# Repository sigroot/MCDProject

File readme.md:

This project is to design a MC68K based microcomputer on a single board.

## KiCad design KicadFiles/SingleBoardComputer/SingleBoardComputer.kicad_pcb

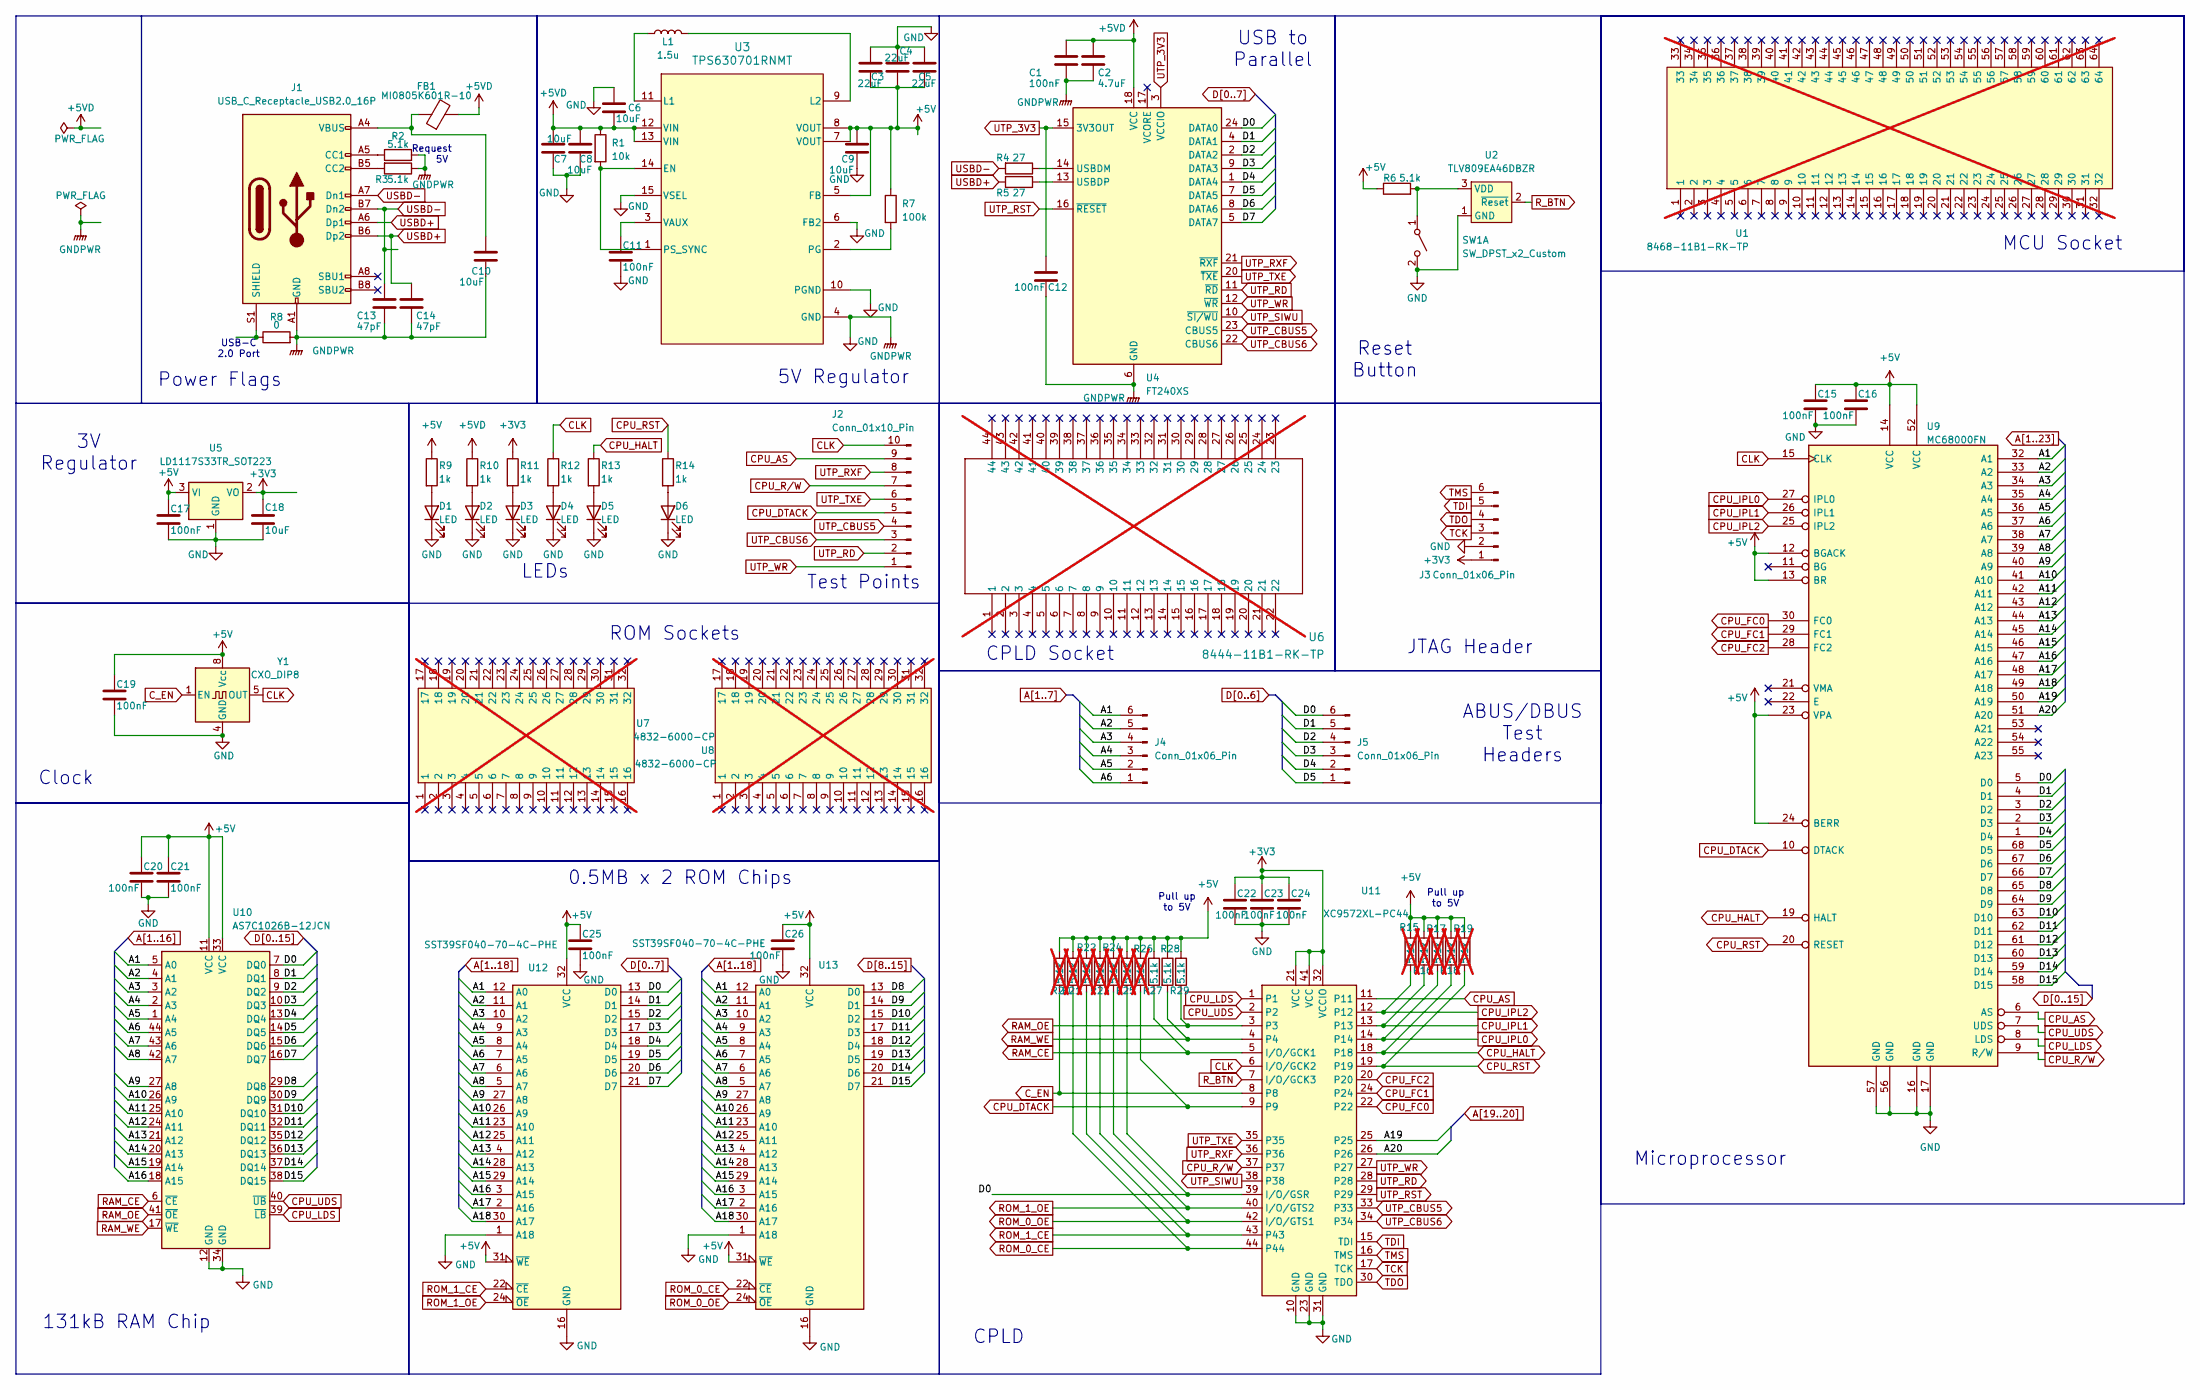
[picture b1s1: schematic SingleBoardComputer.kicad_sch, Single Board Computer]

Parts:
C1, C12, C15, C16, C17, C19, C20, C21, C22, C23, C24, C25, C26: 100nF; C_0603_1608Metric_Pad1.08x0.95mm_HandSolder
C2: 4.7uF; C_0603_1608Metric_Pad1.08x0.95mm_HandSolder
C3, C4, C5: 22uF; C_0805_2012Metric_Pad1.18x1.45mm_HandSolder
C6, C9: 10uF; C_0603_1608Metric_Pad1.08x0.95mm_HandSolder
C7, C8, C10, C18: 10uF; C_0805_2012Metric_Pad1.18x1.45mm_HandSolder
C11: 100nF; C_0402_1005Metric_Pad0.74x0.62mm_HandSolder; LCSC PN C155422
C13, C14: 47pF; C_0805_2012Metric_Pad1.18x1.45mm_HandSolder
D1, D2, D3, D4, D5, D6: LED; LED_0805_2012Metric_Pad1.15x1.40mm_HandSolder
FB1: MI0805K601R-10; L_0805_2012Metric_Pad1.15x1.40mm_HandSolder
J1: USB_C_Receptacle_USB2.0_16P; CUI_UJ20-C-V-C-3-SMT-TR
J2: Conn_01x10_Pin; PinHeader_1x10_P2.54mm_Vertical
J3, J4, J5: Conn_01x06_Pin; PinHeader_1x06_P2.54mm_Vertical
L1: 1.5u; L_Coilcraft_XxL4020; LCSC PN C3033018
R1: 10k; R_0805_2012Metric_Pad1.20x1.40mm_HandSolder
R2, R3, R6, R27, R28, R29: 5.1k; R_0805_2012Metric_Pad1.20x1.40mm_HandSolder
R4, R5: 27; R_0805_2012Metric_Pad1.20x1.40mm_HandSolder
R7: 100k; R_0805_2012Metric_Pad1.20x1.40mm_HandSolder
R8: 0; R_0805_2012Metric_Pad1.20x1.40mm_HandSolder
R9, R10, R11, R12, R13, R14: 1k; R_0805_2012Metric_Pad1.20x1.40mm_HandSolder
R15, R16, R17, R18, R19, R20, R21, R22, R23, R24, R25, R26: 5.1k; R_0805_2012Metric_Pad1.20x1.40mm_HandSolder; not fitted
SW1: SW_DPST_x2_Custom; SW_SPST_PTS647_Sx38
U1: 8468-11B1-RK-TP; PLCC-68_THT-Socket; not fitted
U2: TLV809EA46DBZR; SOT-23
U3: TPS630701RNMT; RNM0015A; LCSC PN C181473
U4: FT240XS; SSOP-24_3.9x8.7mm_P0.635mm; LCSC PN C69082
U5: LD1117S33TR_SOT223; SOT-223-3_TabPin2; LCSC PN LD1117S33TR
U6: 8444-11B1-RK-TP; TO_11B1-RK-TP_3MM; not fitted
U7, U8: 4832-6000-CP; DIP-32_W15.24mm_Socket; not fitted
U9: MC68000FN; PLCC-68_THT-Socket
U10: AS7C1026B-12JCN; SOJ-44_10.16x28.575mm_P1.27mm
U11: XC9572XL-PC44; PLCC-44_THT-Socket
U12, U13: SST39SF040-70-4C-PHE; DIP-32_W15.24mm_Socket_LongPads
Y1: CXO_DIP8; Oscillator_DIP-8

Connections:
+3V3: C18.1, C22.1, C23.1, C24.1, J3.1, R11.1, U5.2 (VO), U11.21 (VCC), U11.32 (VCCIO), U11.41 (VCC)
+5V: C3.2, C4.2, C5.2, C9.1, C15.1, C16.1, C17.1, C19.1, C20.1, C21.1, C25.1, C26.1, R6.1, R7.1, R9.1, R15.1, R16.1, R17.1, R18.1, R19.1, R20.1, R21.1, R22.1, R23.1, R24.1, R25.1, R26.1, R27.1, R28.1, R29.1, U3.5 (FB), U3.7 (VOUT), U3.8 (VOUT), U5.3 (VI), U9.12 (BGACK), U9.13 (BR), U9.14 (VCC), U9.23 (VPA), U9.24 (BERR), U9.52 (VCC), U10.11 (VCC), U10.33 (VCC), U12.31 (~WE), U12.32 (VCC), U13.31 (~WE), U13.32 (VCC), Y1.8 (Vcc)
+5VD: C1.1, C2.1, C6.2, C7.1, C8.1, FB1.2, R1.1, R10.1, U3.12 (VIN), U3.13 (VIN), U4.18 (VCC)
A1: J4.6, U9.32 (A1), U10.5 (A0), U12.12 (A0), U13.12 (A0)
A2: J4.5, U9.33 (A2), U10.4 (A1), U12.11 (A1), U13.11 (A1)
A3: J4.4, U9.34 (A3), U10.3 (A2), U12.10 (A2), U13.10 (A2)
A4: J4.3, U9.35 (A4), U10.2 (A3), U12.9 (A3), U13.9 (A3)
A5: J4.2, U9.36 (A5), U10.1 (A4), U12.8 (A4), U13.8 (A4)
A6: J4.1, U9.37 (A6), U10.44 (A5), U12.7 (A5), U13.7 (A5)
A7: U9.38 (A7), U10.43 (A6), U12.6 (A6), U13.6 (A6)
A8: U9.39 (A8), U10.42 (A7), U12.5 (A7), U13.5 (A7)
A9: U9.40 (A9), U10.27 (A8), U12.27 (A8), U13.27 (A8)
A10: U9.41 (A10), U10.26 (A9), U12.26 (A9), U13.26 (A9)
A11: U9.42 (A11), U10.25 (A10), U12.23 (A10), U13.23 (A10)
A12: U9.43 (A12), U10.24 (A11), U12.25 (A11), U13.25 (A11)
A13: U9.44 (A13), U10.21 (A12), U12.4 (A12), U13.4 (A12)
A14: U9.45 (A14), U10.20 (A13), U12.28 (A13), U13.28 (A13)
A15: U9.46 (A15), U10.19 (A14), U12.29 (A14), U13.29 (A14)
A16: U9.47 (A16), U10.18 (A15), U12.3 (A15), U13.3 (A15)
A17: U9.48 (A17), U12.2 (A16), U13.2 (A16)
A18: U9.49 (A18), U12.30 (A17), U13.30 (A17)
A19: U9.50 (A19), U11.25
A20: U9.51 (A20), U11.26
CLK: J2.10, R12.1, U9.15 (CLK), U11.6 (I/O/GCK2), Y1.5 (OUT)
CPU_AS: J2.9, U9.6 (AS), U11.11
CPU_DTACK: J2.5, R26.2, U9.10 (DTACK), U11.9
CPU_FC0: U9.30 (FC0), U11.22
CPU_FC1: U9.29 (FC1), U11.24
CPU_FC2: U9.28 (FC2), U11.20
CPU_HALT: R13.1, R18.2, U9.19 (HALT), U11.18
CPU_IPL0: R17.2, U9.27 (IPL0), U11.14
CPU_IPL1: R16.2, U9.26 (IPL1), U11.13
CPU_IPL2: R15.2, U9.25 (IPL2), U11.12
CPU_LDS: U9.8 (LDS), U10.39 (~LB), U11.1
CPU_RST: R14.1, R19.2, U9.20 (RESET), U11.19
CPU_R/W: J2.7, U9.9 (R/W), U11.37
CPU_UDS: U9.7 (UDS), U10.40 (~UB), U11.2
C_EN: R20.2, U11.8, Y1.1 (EN)
D0: J5.6, R25.2, U4.24 (DATA0), U9.5 (D0), U10.7 (DQ0), U11.39 (I/O/GSR), U12.13 (D0)
D1: J5.5, U4.4 (DATA1), U9.4 (D1), U10.8 (DQ1), U12.14 (D1)
D2: J5.4, U4.2 (DATA2), U9.3 (D2), U10.9 (DQ2), U12.15 (D2)
D3: J5.3, U4.9 (DATA3), U9.2 (D3), U10.10 (DQ3), U12.17 (D3)
D4: J5.2, U4.1 (DATA4), U9.1 (D4), U10.13 (DQ4), U12.18 (D4)
D5: J5.1, U4.7 (DATA5), U9.68 (D5), U10.14 (DQ5), U12.19 (D5)
D6: U4.8 (DATA6), U9.67 (D6), U10.15 (DQ6), U12.20 (D6)
D7: U4.5 (DATA7), U9.66 (D7), U10.16 (DQ7), U12.21 (D7)
D8: U9.65 (D8), U10.29 (DQ8), U13.13 (D0)
D9: U9.64 (D9), U10.30 (DQ9), U13.14 (D1)
D10: U9.63 (D10), U10.31 (DQ10), U13.15 (D2)
D11: U9.62 (D11), U10.32 (DQ11), U13.17 (D3)
D12: U9.61 (D12), U10.35 (DQ12), U13.18 (D4)
D13: U9.60 (D13), U10.36 (DQ13), U13.19 (D5)
D14: U9.59 (D14), U10.37 (DQ14), U13.20 (D6)
D15: U9.58 (D15), U10.38 (DQ15), U13.21 (D7)
GND: C1.2, C2.2, C3.1, C4.1, C5.1, C6.1, C7.2, C8.2, C9.2, C10.2, C11.2, C12.2, C13.2, C14.2, C15.2, C16.2, C17.2, C18.2, C19.2, C20.2, C21.2, C22.2, C23.2, C24.2, C25.2, C26.2, D1.1 (K), D2.1 (K), D3.1 (K), D4.1 (K), D5.1 (K), D6.1 (K), J1.A1 (GND), J1.A12 (GND), J1.B1 (GND), J1.B12 (GND), J3.2, R2.2, R3.1, R8.2, SW1.2 (B), U2.1 (GND), U3.4 (GND), U3.6 (FB2), U3.10 (PGND), U3.15 (VSEL), U4.6 (GND), U4.19 (GND), U5.1 (GND), U9.16 (GND), U9.17 (GND), U9.56 (GND), U9.57 (GND), U10.12 (GND), U10.34 (GND), U11.10 (GND), U11.23 (GND), U11.31 (GND), U12.1 (A18), U12.16 (GND), U13.1 (A18), U13.16 (GND), Y1.4 (GND)
unnamed: C10.1, FB1.1, J1.A4 (VBUS), J1.A9 (VBUS), J1.B4 (VBUS), J1.B9 (VBUS)
unnamed: D1.2 (A), R9.2
unnamed: D2.2 (A), R10.2
unnamed: D3.2 (A), R11.2
unnamed: D4.2 (A), R12.2
unnamed: D5.2 (A), R13.2
unnamed: D6.2 (A), R14.2
unnamed: J1.A5 (CC1), R2.1
unnamed: J1.B5 (CC2), R3.2
unnamed: J1.S1 (SHIELD), R8.1
unnamed: R6.2, SW1.1 (A), U2.3 (VDD)
unnamed: R1.2, U3.1 (PS_SYNC), U3.14 (EN)
unnamed: L1.1, U3.11 (L1)
unnamed: L1.2, U3.9 (L2)
unnamed: R7.2, U3.2 (PG)
unnamed: C11.1, U3.3 (VAUX)
unnamed: R4.1, U4.14 (USBDM)
unnamed: R5.1, U4.13 (USBDP)
RAM_CE: R27.2, U10.6 (~CE), U11.5 (I/O/GCK1)
RAM_OE: R29.2, U10.41 (~OE), U11.3
RAM_WE: R28.2, U10.17 (~WE), U11.4
ROM_0_CE: R21.2, U11.44, U13.22 (~CE)
ROM_0_OE: R23.2, U11.42 (I/O/GTS1), U13.24 (~OE)
ROM_1_CE: R22.2, U11.43, U12.22 (~CE)
ROM_1_OE: R24.2, U11.40 (I/O/GTS2), U12.24 (~OE)
R_BTN: U2.2 (~Reset), U11.7 (I/O/GCK3)
TCK: J3.3, U11.17 (TCK)
TDI: J3.5, U11.15 (TDI)
TDO: J3.4, U11.30 (TDO)
TMS: J3.6, U11.16 (TMS)
USBD+: C14.1, J1.A6 (Dp1), J1.B6 (Dp2), R5.2
USBD-: C13.1, J1.A7 (Dn1), J1.B7 (Dn2), R4.2
UTP_3V3: C12.1, U4.3 (VCCIO), U4.15 (3V3OUT)
UTP_CBUS5: J2.4, U4.23 (CBUS5), U11.33
UTP_CBUS6: J2.3, U4.22 (CBUS6), U11.34
UTP_RD: J2.2, U4.11 (~RD), U11.28
UTP_RST: U4.16 (~RESET), U11.29
UTP_RXF: J2.8, U4.21 (~RXF), U11.36
UTP_SIWU: U4.10 (~SI/WU), U11.38
UTP_TXE: J2.6, U4.20 (~TXE), U11.35
UTP_WR: J2.1, U4.12 (~WR), U11.27

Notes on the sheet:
Power Flags
USB to Parallel
USB-C 2.0 Port
Test Points
Request 5V
5V Regulator
Reset Button
ABUS/DBUS Test Headers
0.5MB x 2 ROM Chips
CPLD Socket
131kB RAM Chip
CPLD
Clock
Pull up to 5V
ROM Sockets
3V Regulator
Microprocessor
MCU Socket
LEDs
JTAG Header

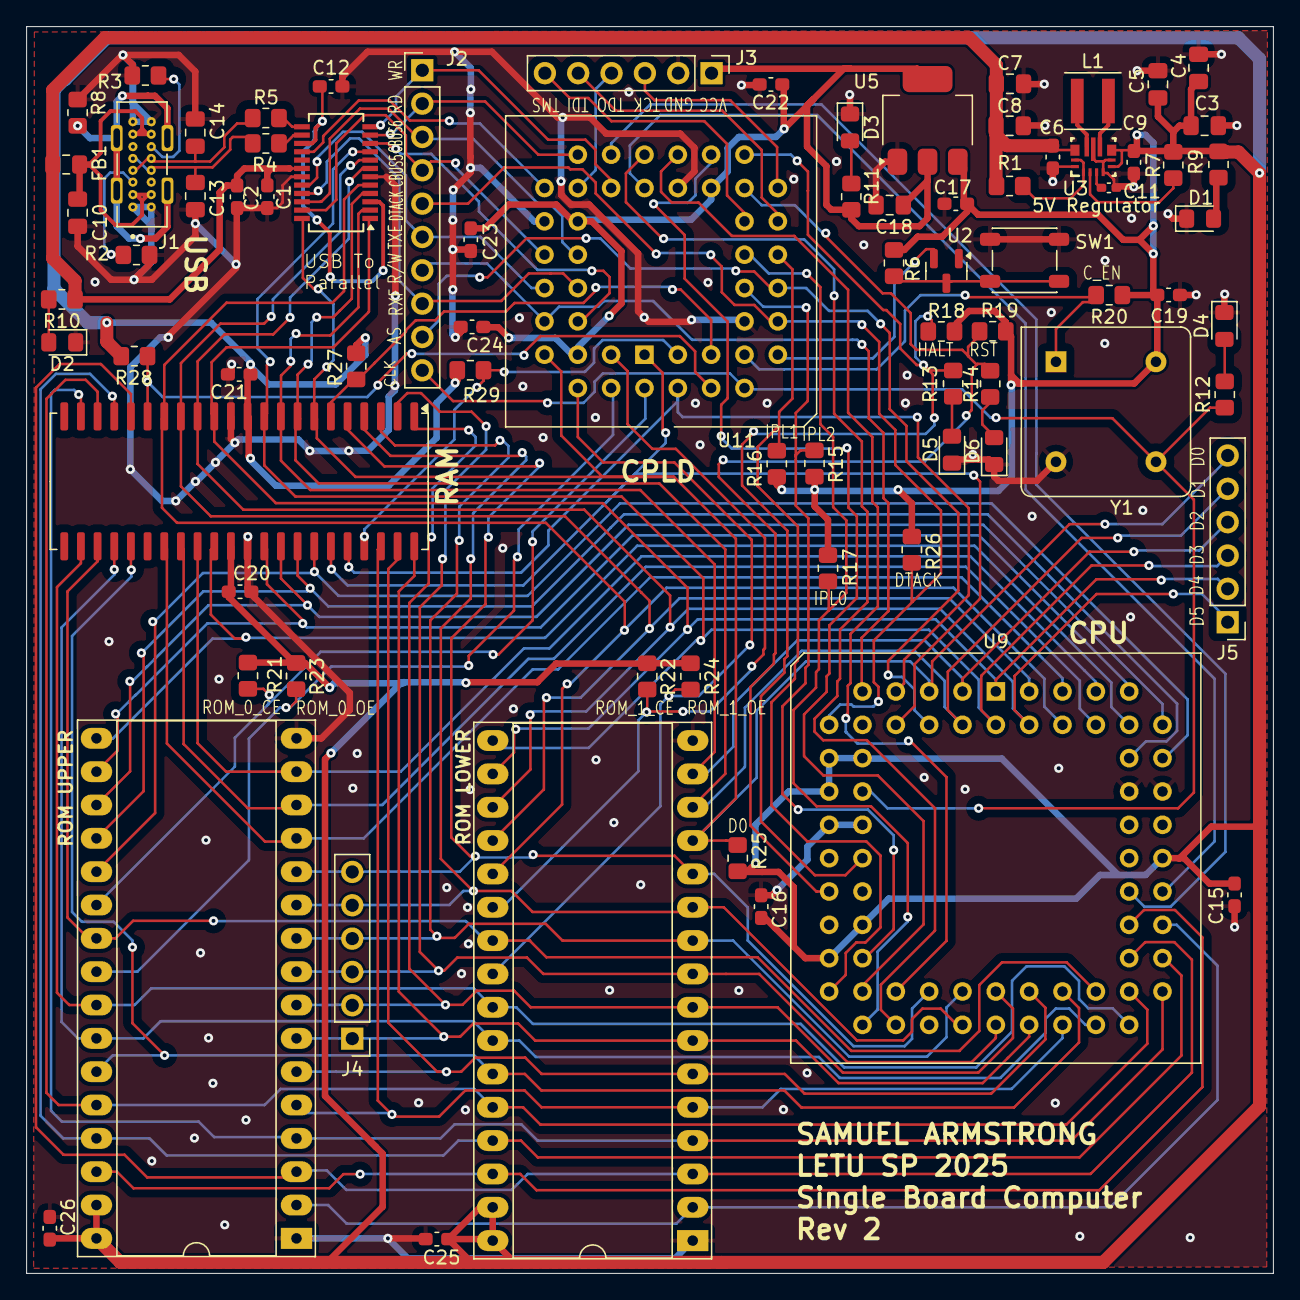
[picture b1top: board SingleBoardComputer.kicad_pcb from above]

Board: 2 copper layers, 95.0 x 95.0 mm, 79 parts (0 on the bottom side), 96 nets.

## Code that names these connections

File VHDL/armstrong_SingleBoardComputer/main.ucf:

#PACE: Start of Constraints generated by PACE

#PACE: Start of PACE I/O Pin Assignments
NET "A<19>"  LOC = "P25"  ;
NET "A<20>"  LOC = "P26"  ;
NET "C_EN"  LOC = "P8"  ;
NET "CLK"  LOC = "P6"  ;
NET "CPU_AS"  LOC = "P11"  ;
NET "CPU_DTACK"  LOC = "P9"  ;
NET "CPU_FC0"  LOC = "P22"  ;
NET "CPU_FC1"  LOC = "P24"  ;
NET "CPU_FC2"  LOC = "P20"  ;
NET "CPU_HALT"  LOC = "P18"  ;
NET "CPU_IPL0"  LOC = "P14"  ;
NET "CPU_IPL1"  LOC = "P13"  ;
NET "CPU_IPL2"  LOC = "P12"  ;
NET "CPU_LDS"  LOC = "P1"  ;
NET "CPU_R_W"  LOC = "P37"  ;
NET "CPU_RST"  LOC = "P19"  ;
NET "CPU_UDS"  LOC = "P2"  ;
NET "D0"  LOC = "P39"  ;
NET "R_BTN"  LOC = "P7"  ;
NET "RAM_CE"  LOC = "P5"  ;
NET "RAM_OE"  LOC = "P3"  ;
NET "RAM_WE"  LOC = "P4"  ;
NET "ROM_0_CE"  LOC = "P44"  ;
NET "ROM_0_OE"  LOC = "P42"  ;
NET "ROM_1_CE"  LOC = "P43"  ;
NET "ROM_1_OE"  LOC = "P40"  ;
NET "UTP_CBUS5"  LOC = "P33"  ;
NET "UTP_CBUS6"  LOC = "P34"  ;
NET "UTP_RD"  LOC = "P28"  ;
NET "UTP_RST"  LOC = "P29"  ;
NET "UTP_RXF"  LOC = "P36"  ;
NET "UTP_SIWU"  LOC = "P38"  ;
NET "UTP_TXE"  LOC = "P35"  ;
NET "UTP_WR"  LOC = "P27"  ;

#PACE: Start of PACE Area Constraints

#PACE: Start of PACE Prohibit Constraints

#PACE: End of Constraints generated by PACE

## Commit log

2025-01-13 updated time_management
2025-01-23 Week 1 Done
2025-01-26 Schematic v1.0 done
2025-01-29 Schematic V2.0
2025-02-03 Changed 5V regulator to TPS63070 (which JLCPCB can provide and solder)
2025-02-05 Updated some schematic, added sockets to BOM, building PCB
2025-02-10 PCB before schematic modification
2025-02-12 Schematic after corrections
2025-02-13 Correction Corrections
2025-02-15 PCB done
2025-02-18 Purchase 1
2025-03-16 Backup after working board
2025-03-24 Cleaning Directories
2025-04-10 Working Main Menu
2025-04-14 Monitor done?
2025-04-20 included VHDL
2025-04-24 Completed Demonstration
